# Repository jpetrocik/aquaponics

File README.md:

# Aquaponic's Firmware For Sonoff Dual R2

Firmware to control an aquaponics system using Sonoff Dual R2.  The Sonoff Dual R2 has two relays to control the pumps, the firmware acts as a timer to control the rely and provides a RestApi to control the pumps from OpenHab or HomeAssistant. The Sonoff curcuit board is removed from the orginal Sonoff enclosure and put into a weather proof enclosure ordered from Amazon.

### Sonoff Dual R2

## Flashing Firmware

The Sonoff uses a ESP8266 Wifi chip, so this section discusses flashing the ESP8266 chip on the Sonoff Dual R2. For more details google: "Arduino ESP8266"

### Setup the Arduino IDE

* Download Arduino IDE.

* Open you IDE and click on "File -> Preferences".

* In  "Aditional Boards Manager URLs" add this line and click on "OK": "http://arduino.esp8266.com/stable/package_esp8266com_index.json"

* Go to "Tools -> Board -> Boards Manager", type "ESP8266" and install it.

* Go again to "Tools -> Board" and select "Generic ESP8266 Module".

### Flashing

* Place a jumper on the pins labeled BUTTON 0 and GND, without this the Sonoff does not enter flash mode.

* Connect the TTL programmer to programming header pins on the Sonoff.  You must cross over the RX->TX and TX-RX.  So from the promgrammer connect TX -> RX on the Sonoff and RX to TX on the Sonoff.  Connect 3.3v and GND.

* Plug in the programmer your computer.

* Using Adruino IDE, open "firmware.ino" from this project.

* From the menu: Tool -> Boards -> "Generic ESP8266 Module"

* After selecting the board change the following defaults from the Tool menu:

Flash Mode: DOUT (compatiable)

Flash Size: 1M (no spiff)

Port: \<select your programmer from the list\>

* Programming the Sonoff by clickign to "Upload" icon

## Sonoff Dual R2 Programming Headers 

## Enclosure

## Programmer

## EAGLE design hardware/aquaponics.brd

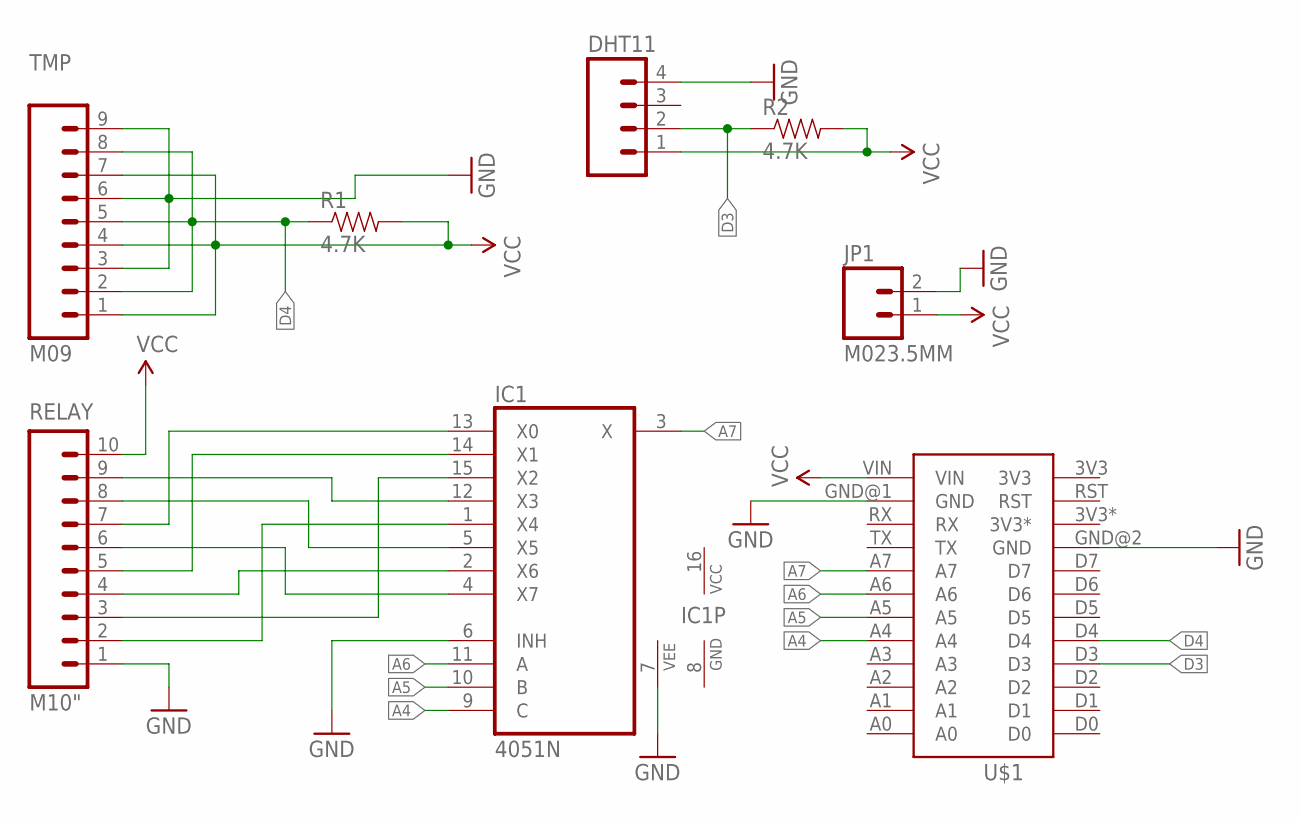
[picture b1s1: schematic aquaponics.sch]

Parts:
DHT11: M04PTH; 1X04
IC1: 4051N; DIL16
JP1: M023.5MM; SCREWTERMINAL-3.5MM-2
R1, R2: 4.7K; 1206
RELAY: M10"; 1X10
TMP: M09; 1X09
U$1: SPARKCORE

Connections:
A4: IC1.9 (C), U$1.A4
A5: IC1.10 (B), U$1.A5
A6: IC1.11 (A), U$1.A6
A7: IC1.3 (X), U$1.A7
D3: DHT11.2, R2.1, U$1.D3
D4: R1.1, TMP.2, TMP.5, TMP.8, U$1.D4
GND: DHT11.4, IC1.6 (INH), IC1.7 (VEE), IC1.8 (GND), JP1.2, RELAY.1, TMP.3, TMP.6, TMP.9, U$1.GND@1 (GND), U$1.GND@2 (GND)
unnamed: IC1.4 (X7), RELAY.6
unnamed: IC1.2 (X6), RELAY.4
unnamed: IC1.15 (X2), RELAY.3
unnamed: IC1.1 (X4), RELAY.2
unnamed: IC1.14 (X1), RELAY.5
unnamed: IC1.13 (X0), RELAY.7
unnamed: IC1.5 (X5), RELAY.8
unnamed: IC1.12 (X3), RELAY.9
VCC: DHT11.1, IC1.16 (VCC), JP1.1, R1.2, R2.2, RELAY.10, TMP.1, TMP.4, TMP.7, U$1.VIN

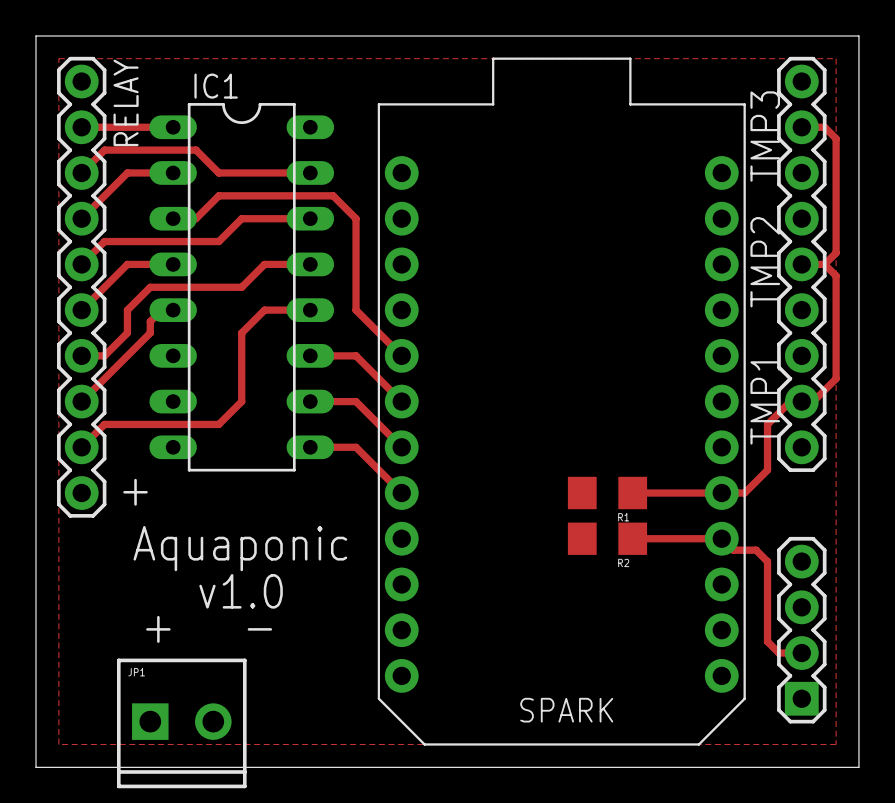
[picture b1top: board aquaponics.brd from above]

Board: 2 copper layers, 45.7 x 40.6 mm, 8 parts (0 on the bottom side), 16 nets.

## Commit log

2014-11-20 Inital commit
2015-06-16 Added heater monitor
2015-06-16 Move firmware files to firmware and added eagle pcb files
2016-01-11 Upgraded OneWire and resolved Timer name conflict
2018-06-12 Added start/stop pump api call
2019-12-01 Moved to Sonoff Dual R2 hardware
2019-12-01 Updated to reflect new hardware
2019-12-01 Adding enclosure image
2019-12-01 Fixed enclosure image link
2019-12-01 Flashing details
2019-12-01 Additianal images
2019-12-01 Flashing instructions

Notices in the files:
parts and their libraries:
SparkFun-Connectors: Licensing: Creative Commons ShareAlike 4.0 International - https://creativecommons.org/licenses/by-sa/4.0
